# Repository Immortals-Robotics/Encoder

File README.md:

# ImmortalsEncoder
Magnetic encoder PCB based on TLE5012

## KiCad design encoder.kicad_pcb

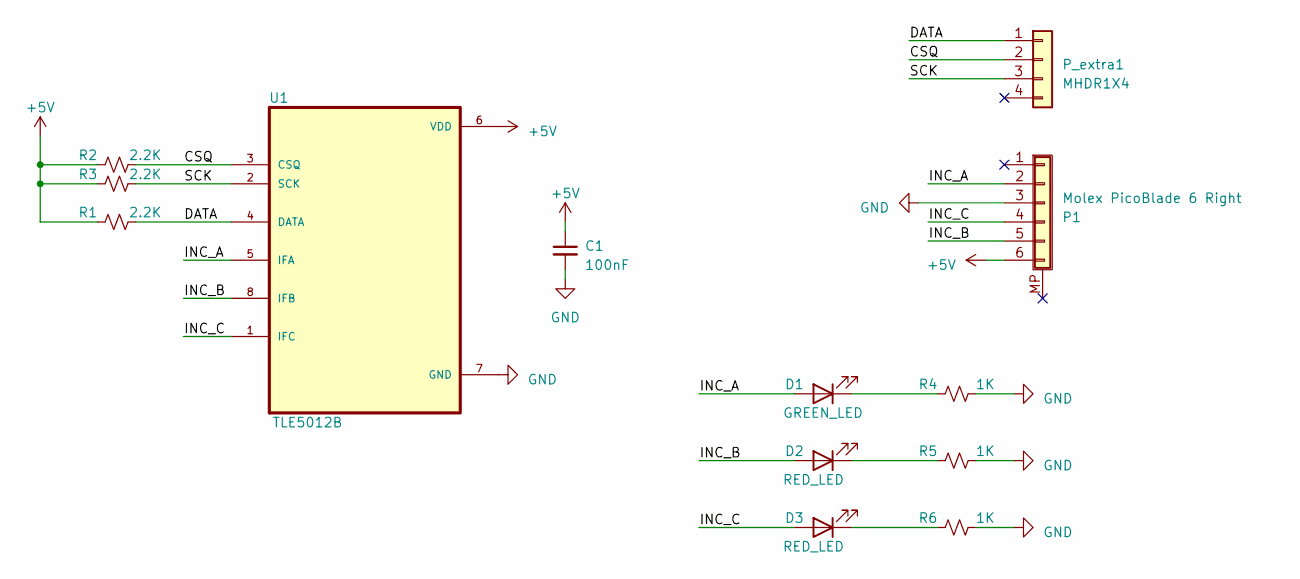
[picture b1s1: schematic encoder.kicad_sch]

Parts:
C1: 100nF; C_0603_1608Metric_Pad1.08x0.95mm_HandSolder
D1: GREEN_LED; LED_0603_1608Metric_Pad1.05x0.95mm_HandSolder
D2, D3: RED_LED; LED_0603_1608Metric_Pad1.05x0.95mm_HandSolder
P1: Molex PicoBlade 6 Right; Molex_PicoBlade_53261-0671_1x06-1MP_P1.25mm_Horizontal
P_extra1: MHDR1X4; PinHeader_1x04_P1.27mm_Horizontal
R1, R2, R3: 2.2K; R_0603_1608Metric_Pad0.98x0.95mm_HandSolder
R4, R5, R6: 1K; R_0603_1608Metric_Pad0.98x0.95mm_HandSolder
U1: TLE5012B; SOIC127P600X175-8N

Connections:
+5V: C1.1, P1.6, R1.1, R2.1, R3.1, U1.6 (VDD)
/CSQ: P_extra1.2, R2.2, U1.3 (CSQ)
/DATA: P_extra1.1, R1.2, U1.4 (DATA)
/INC_A: D1.2 (A), P1.2, U1.5 (IFA)
/INC_B: D2.2 (A), P1.5, U1.8 (IFB)
/INC_C: D3.2 (A), P1.4, U1.1 (IFC)
/SCK: P_extra1.3, R3.2, U1.2 (SCK)
GND: C1.2, P1.3, R4.2, R5.2, R6.2, U1.7 (GND)
unnamed: D1.1 (K), R4.1
unnamed: D2.1 (K), R5.1
unnamed: D3.1 (K), R6.1

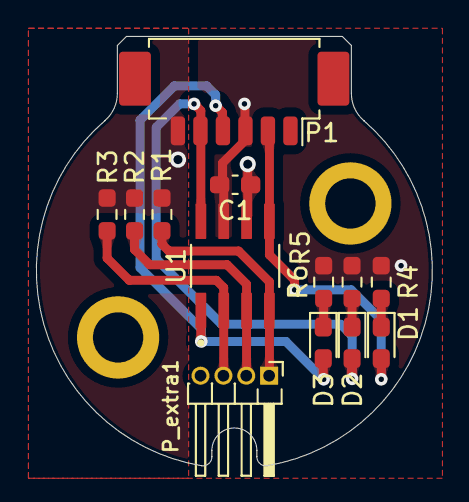
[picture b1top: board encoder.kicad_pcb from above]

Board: 2 copper layers, 22.0 x 23.9 mm, 13 parts (0 on the bottom side), 11 nets.

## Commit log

2023-03-02 Submitting the original design used in robots since 2018.
2023-03-02 Move the project to KiCad from Altium.
2023-04-15 Move to kicad symbols, route INC_C to the main connector.
2023-04-15 Change greber settings to jlcpcb.
2023-04-15 Add output folder to ignores.
2023-05-02 Add teardrops.
2023-05-02 Add version text.
2023-05-02 Generate gerber files.
2023-05-06 V2 of the encoder, which is currently in use.
